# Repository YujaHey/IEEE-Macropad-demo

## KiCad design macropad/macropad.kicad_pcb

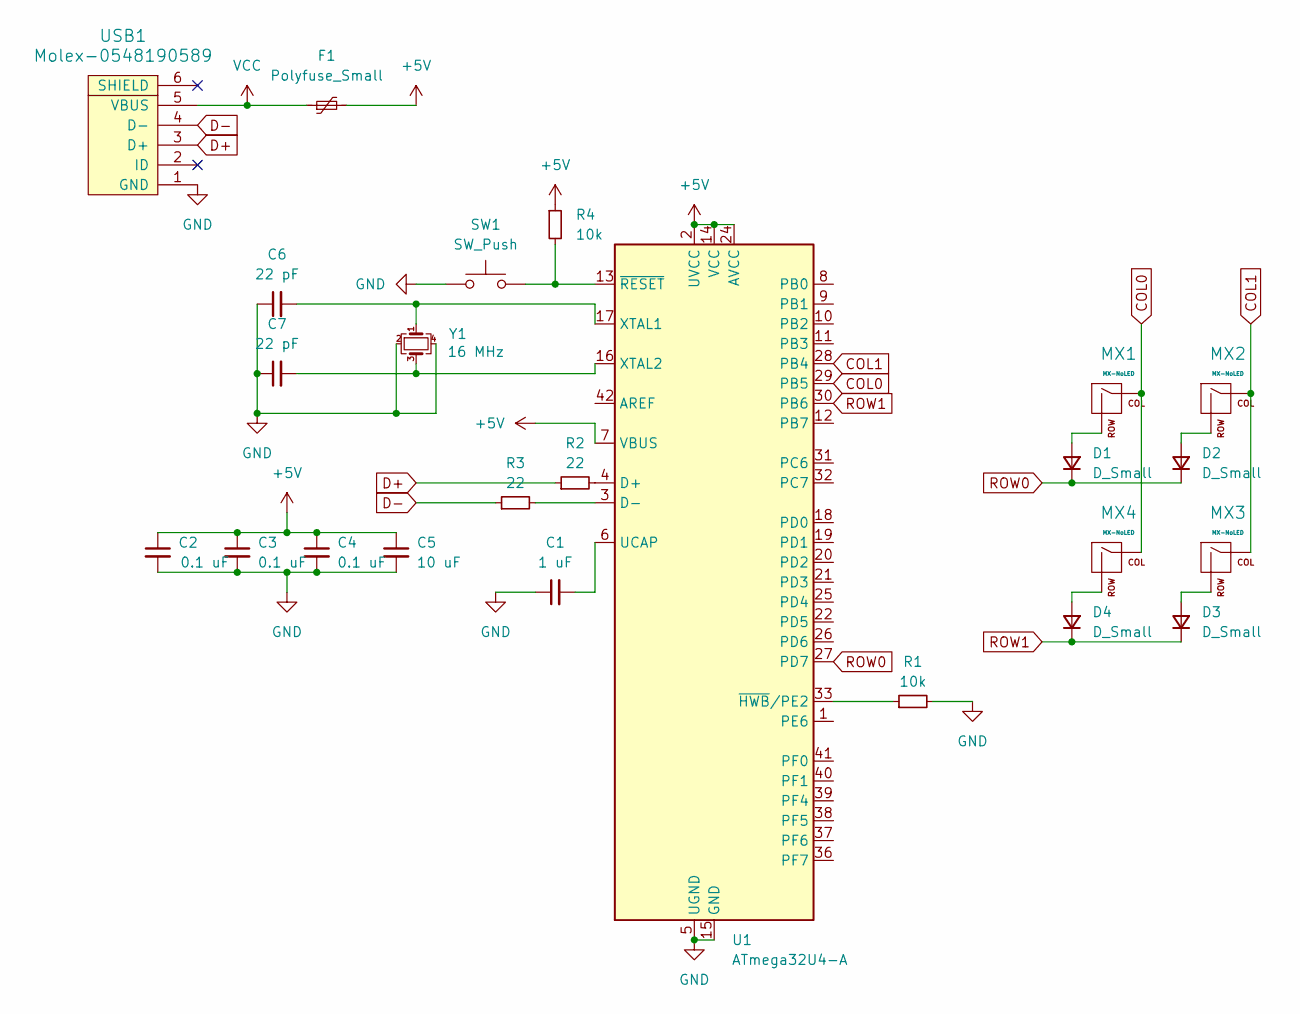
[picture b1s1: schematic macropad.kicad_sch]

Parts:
C1: 1 uF; C_0805_2012Metric
C2, C3, C4: 0.1 uF; C_0805_2012Metric
C5: 10 uF; C_0805_2012Metric
C6, C7: 22 pF; C_0805_2012Metric
D1, D2, D3, D4: D_Small; D_SOD-123
F1: Polyfuse_Small; Fuse_1206_3216Metric
MX1, MX2, MX3, MX4: MX-NoLED; MXOnly-1U-NoLED
R1, R4: 10k; R_0805_2012Metric
R2, R3: 22; R_0805_2012Metric
SW1: SW_Push; SKQG-1155865
U1: ATmega32U4-A; TQFP-44_10x10mm_P0.8mm
USB1: Molex-0548190589
Y1: 16 MHz; Crystal_SMD_3225-4Pin_3.2x2.5mm

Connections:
+5V: C2.1, C3.1, C4.1, C5.1, F1.2, R4.1, U1.2 (UVCC), U1.7 (VBUS), U1.14 (VCC), U1.24 (AVCC), U1.34 (VCC), U1.44 (AVCC)
COL0: MX1.1 (COL), MX4.1 (COL), U1.29 (PB5)
COL1: MX2.1 (COL), MX3.1 (COL), U1.28 (PB4)
D+: R2.1, USB1.3 (D+)
D-: R3.1, USB1.4 (D-)
GND: C1.1, C2.2, C3.2, C4.2, C5.2, C6.1, C7.1, R1.2, SW1.1, U1.5 (UGND), U1.15 (GND), U1.23 (GND), U1.35 (GND), U1.43 (GND), USB1.1 (GND), Y1.2, Y1.4
unnamed: D1.2 (A), MX1.2 (ROW)
unnamed: D2.2 (A), MX2.2 (ROW)
unnamed: D3.2 (A), MX3.2 (ROW)
unnamed: D4.2 (A), MX4.2 (ROW)
unnamed: R2.2, U1.4 (D+)
unnamed: R3.2, U1.3 (D-)
unnamed: C1.2, U1.6 (UCAP)
unnamed: C6.2, U1.17 (XTAL1), Y1.1
unnamed: C7.2, U1.16 (XTAL2), Y1.3
unnamed: R1.1, U1.33 (~HWB/PE2)
unnamed: R4.2, SW1.2, U1.13 (~RESET)
ROW0: D1.1 (K), D2.1 (K), U1.27 (PD7)
ROW1: D3.1 (K), D4.1 (K), U1.30 (PB6)
VCC: F1.1, USB1.5 (VBUS)

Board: 2 copper layers, 24 parts (20 on the bottom side), 20 nets, no tracks yet.

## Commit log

2025-02-05 created project in kicad
2025-02-05 add submodules
2025-02-05 updated libraries within kicad
2025-02-05 schematic editing
2025-02-12 finished schematic
2025-02-12 pcb layout
